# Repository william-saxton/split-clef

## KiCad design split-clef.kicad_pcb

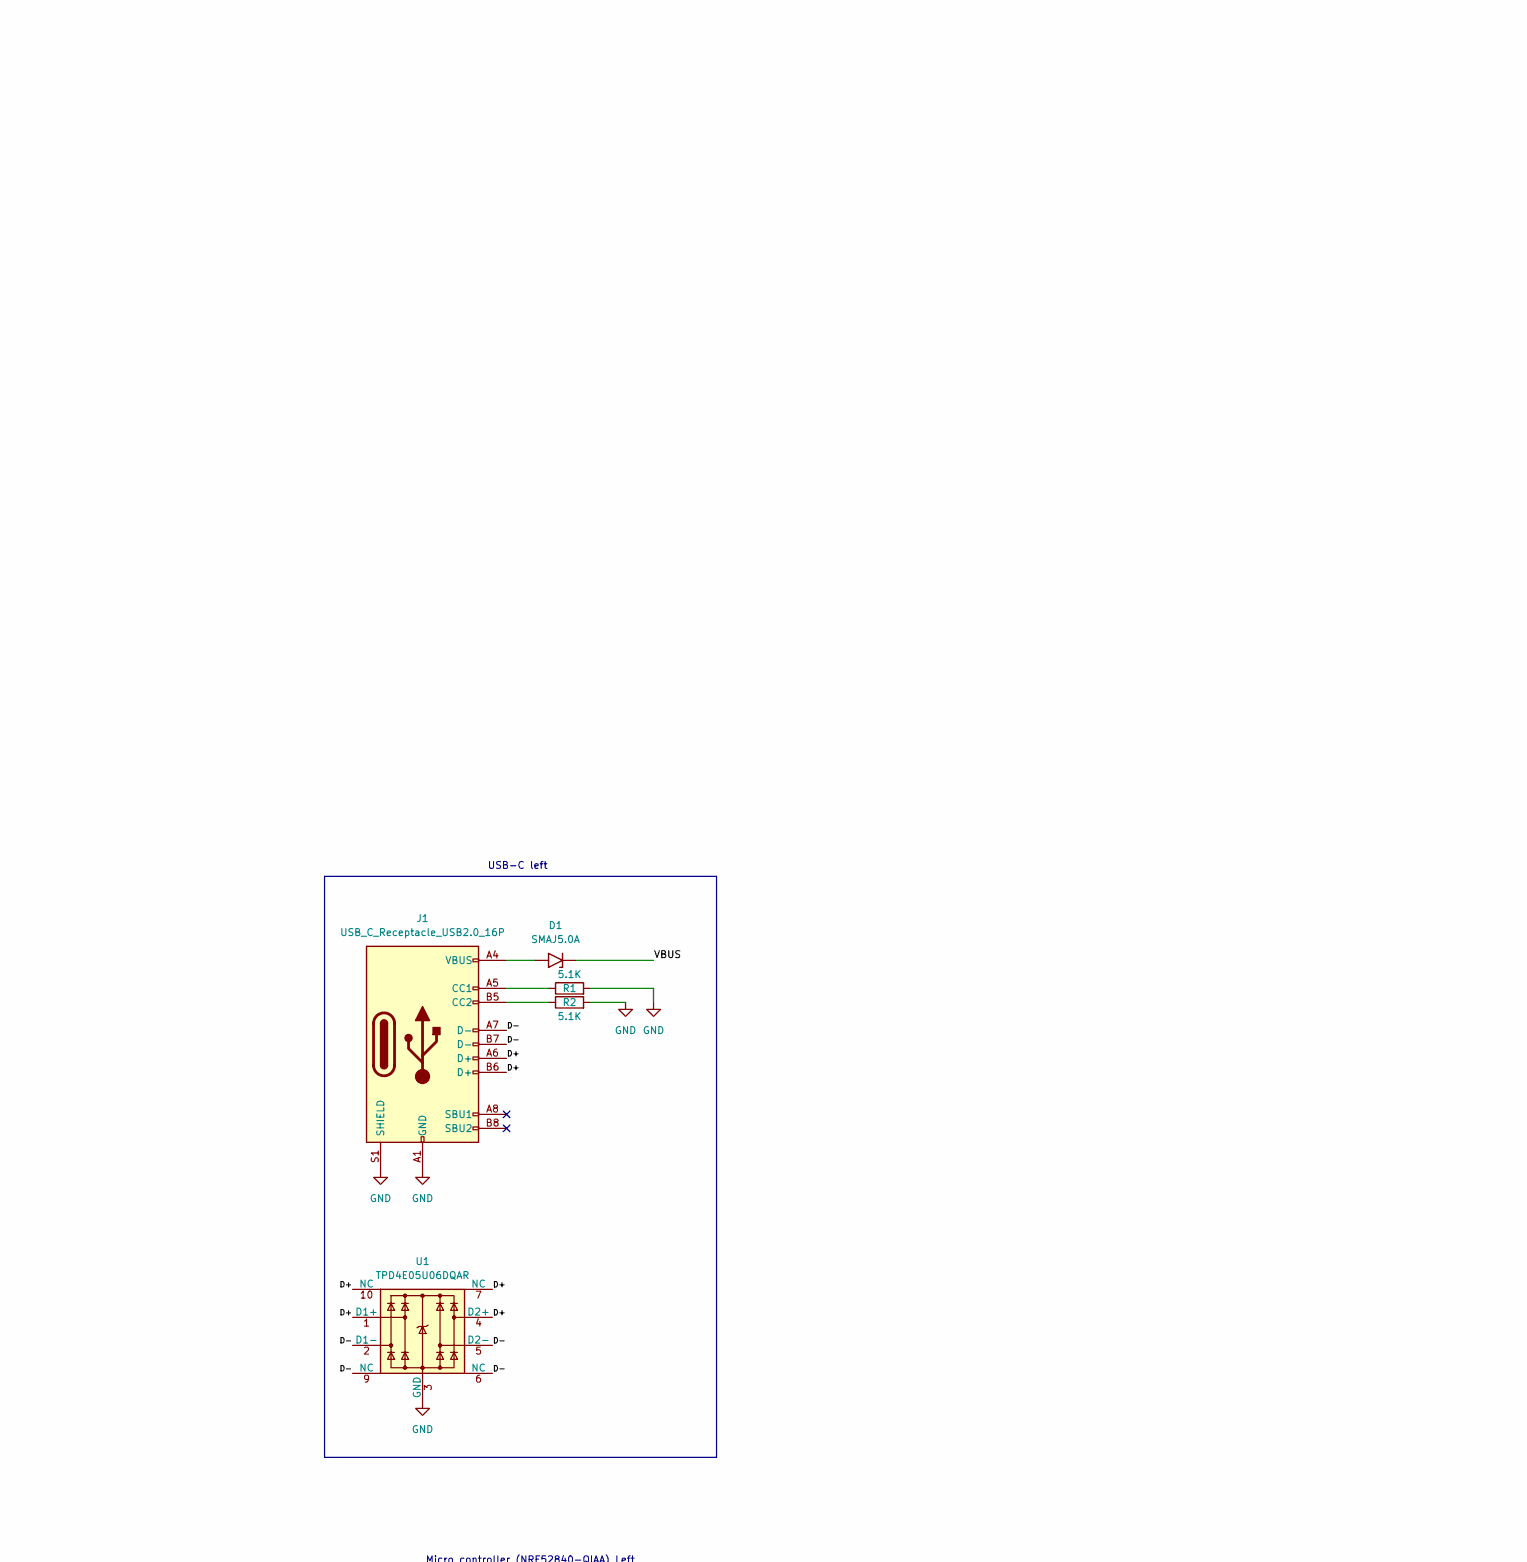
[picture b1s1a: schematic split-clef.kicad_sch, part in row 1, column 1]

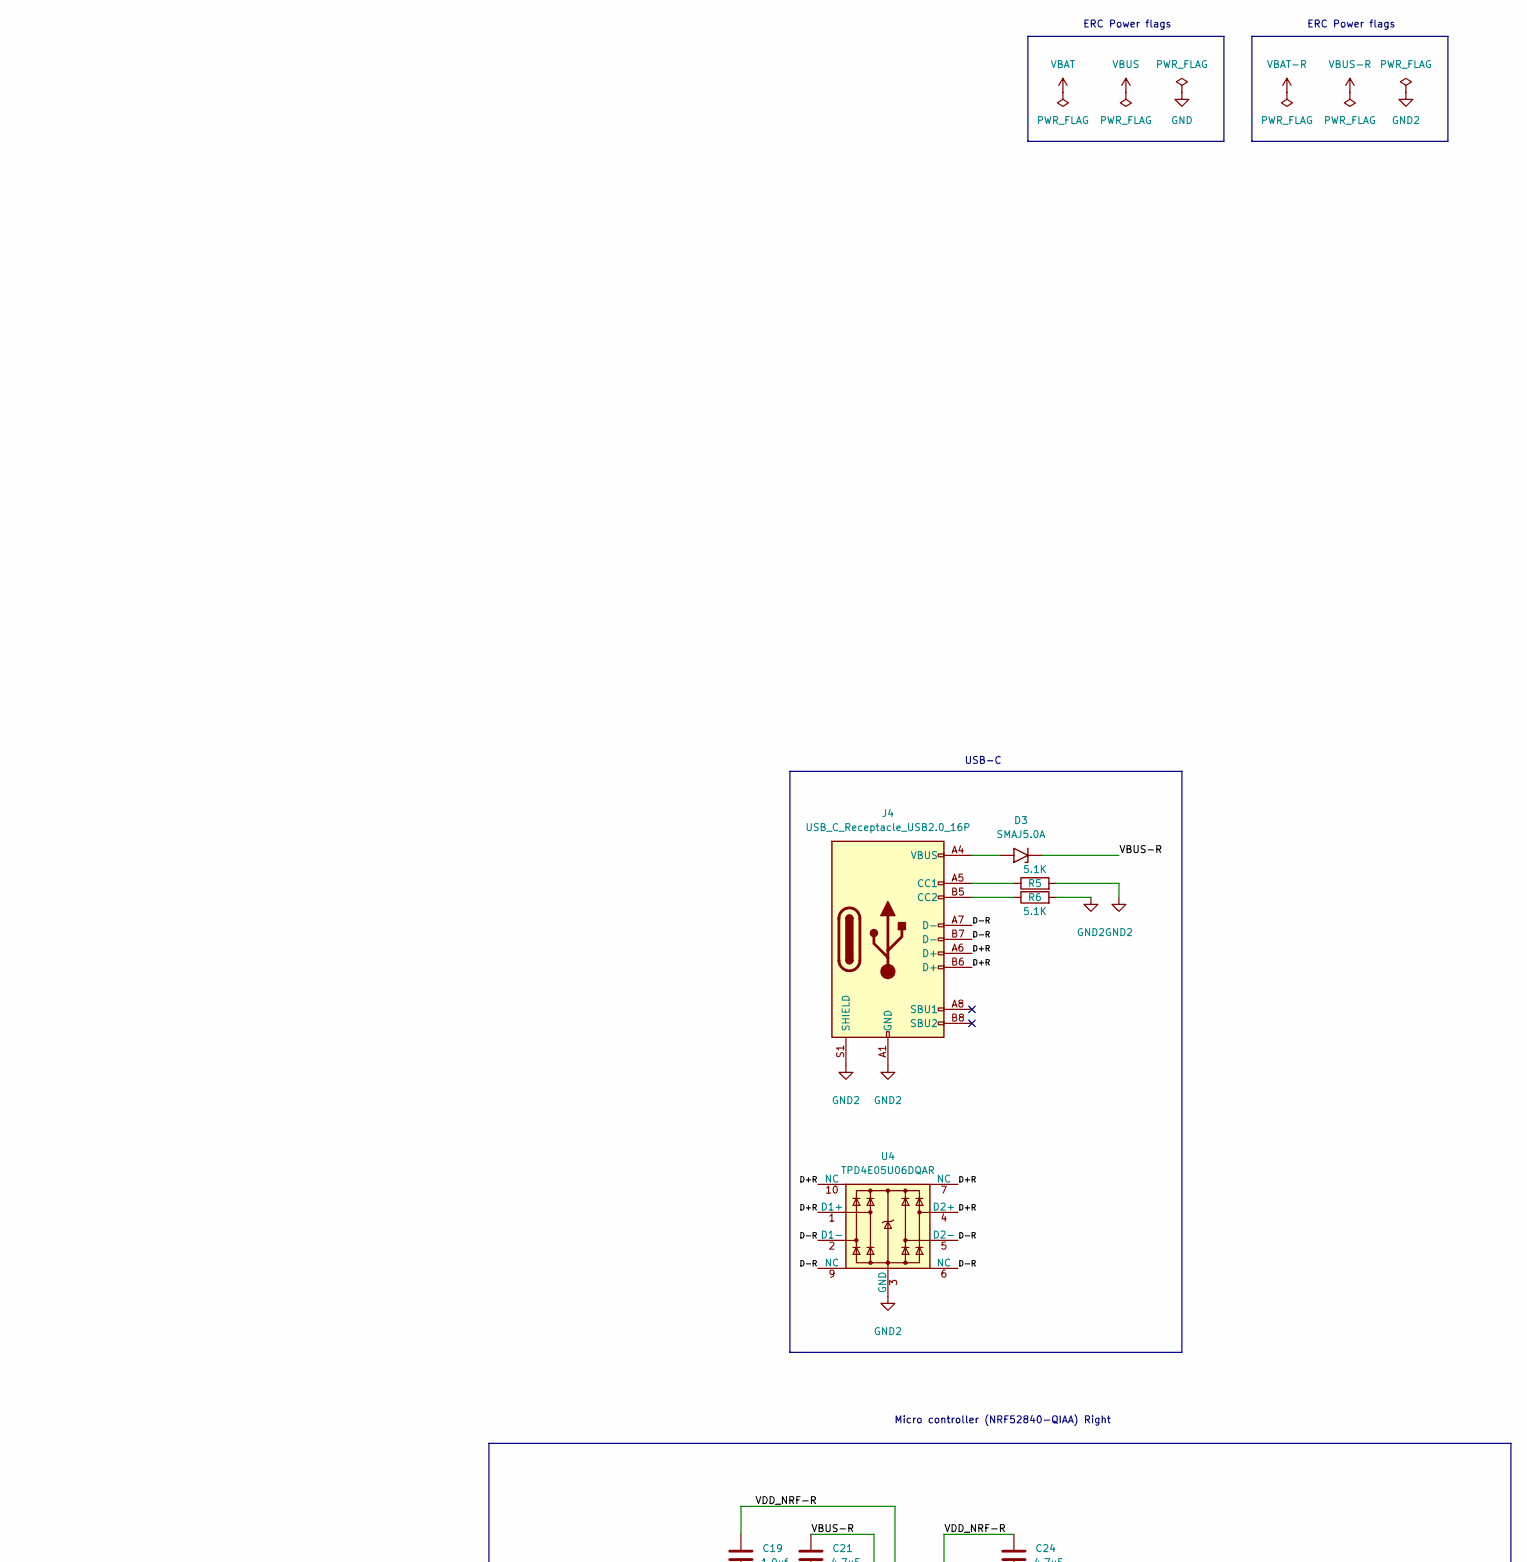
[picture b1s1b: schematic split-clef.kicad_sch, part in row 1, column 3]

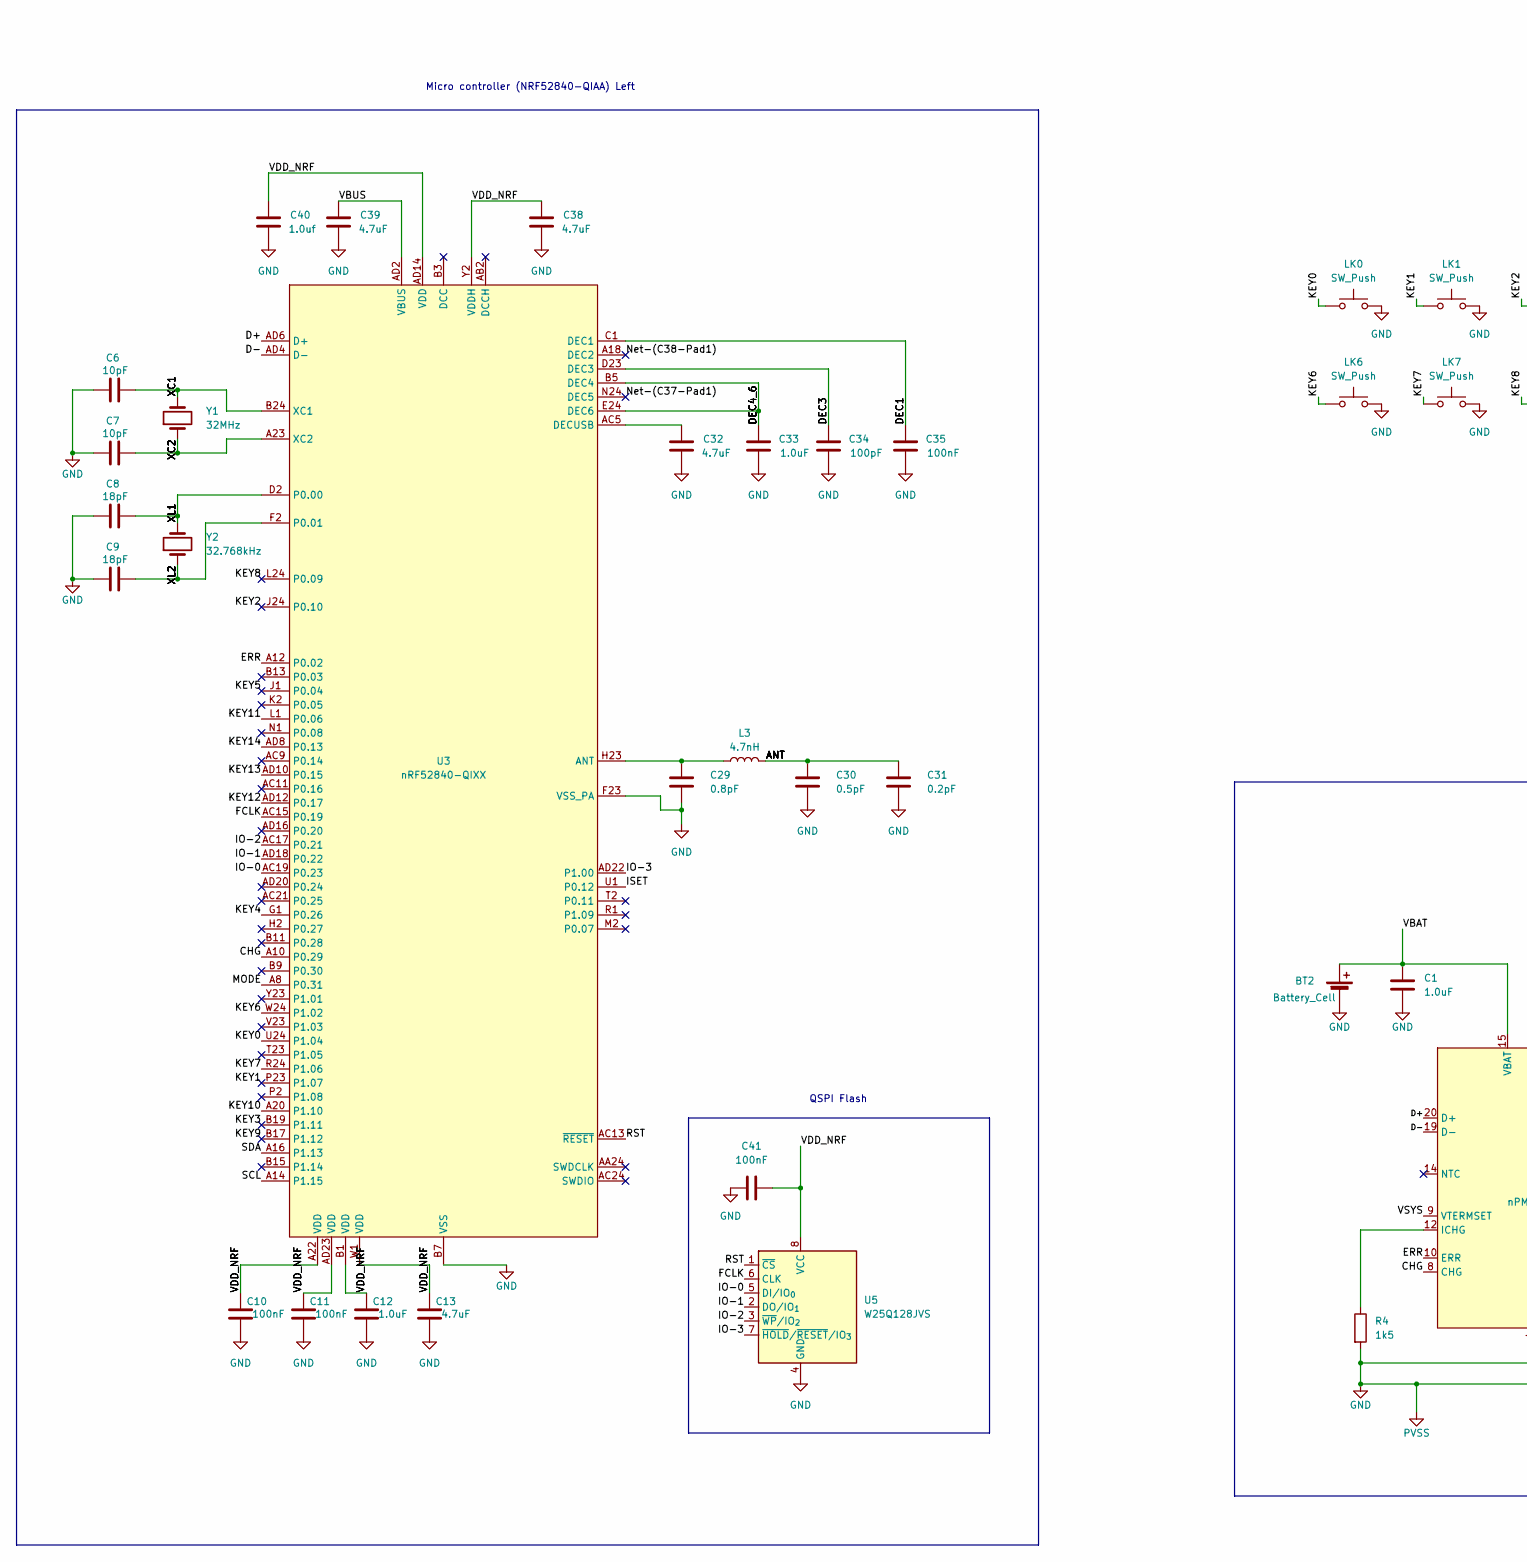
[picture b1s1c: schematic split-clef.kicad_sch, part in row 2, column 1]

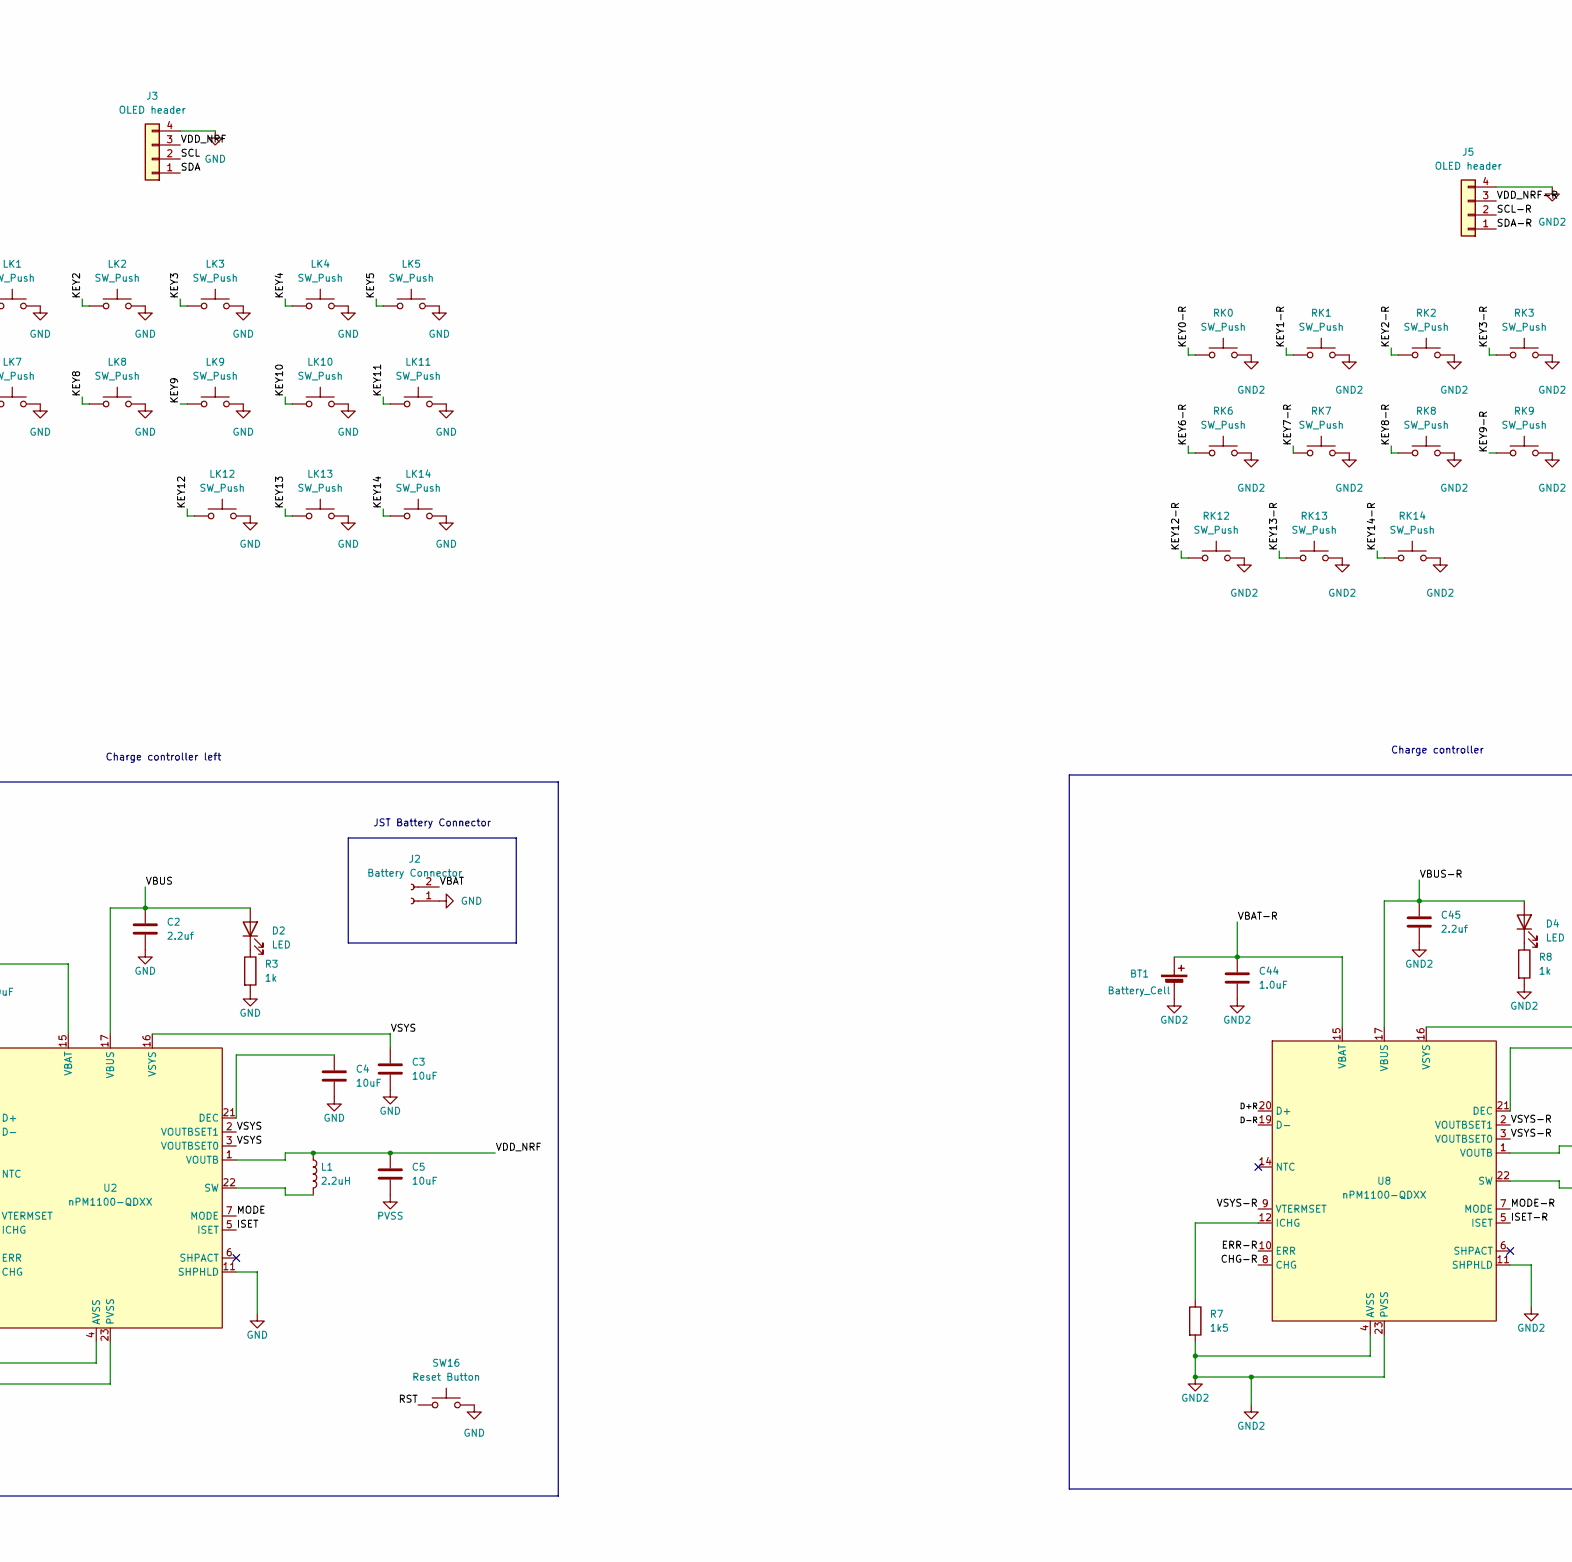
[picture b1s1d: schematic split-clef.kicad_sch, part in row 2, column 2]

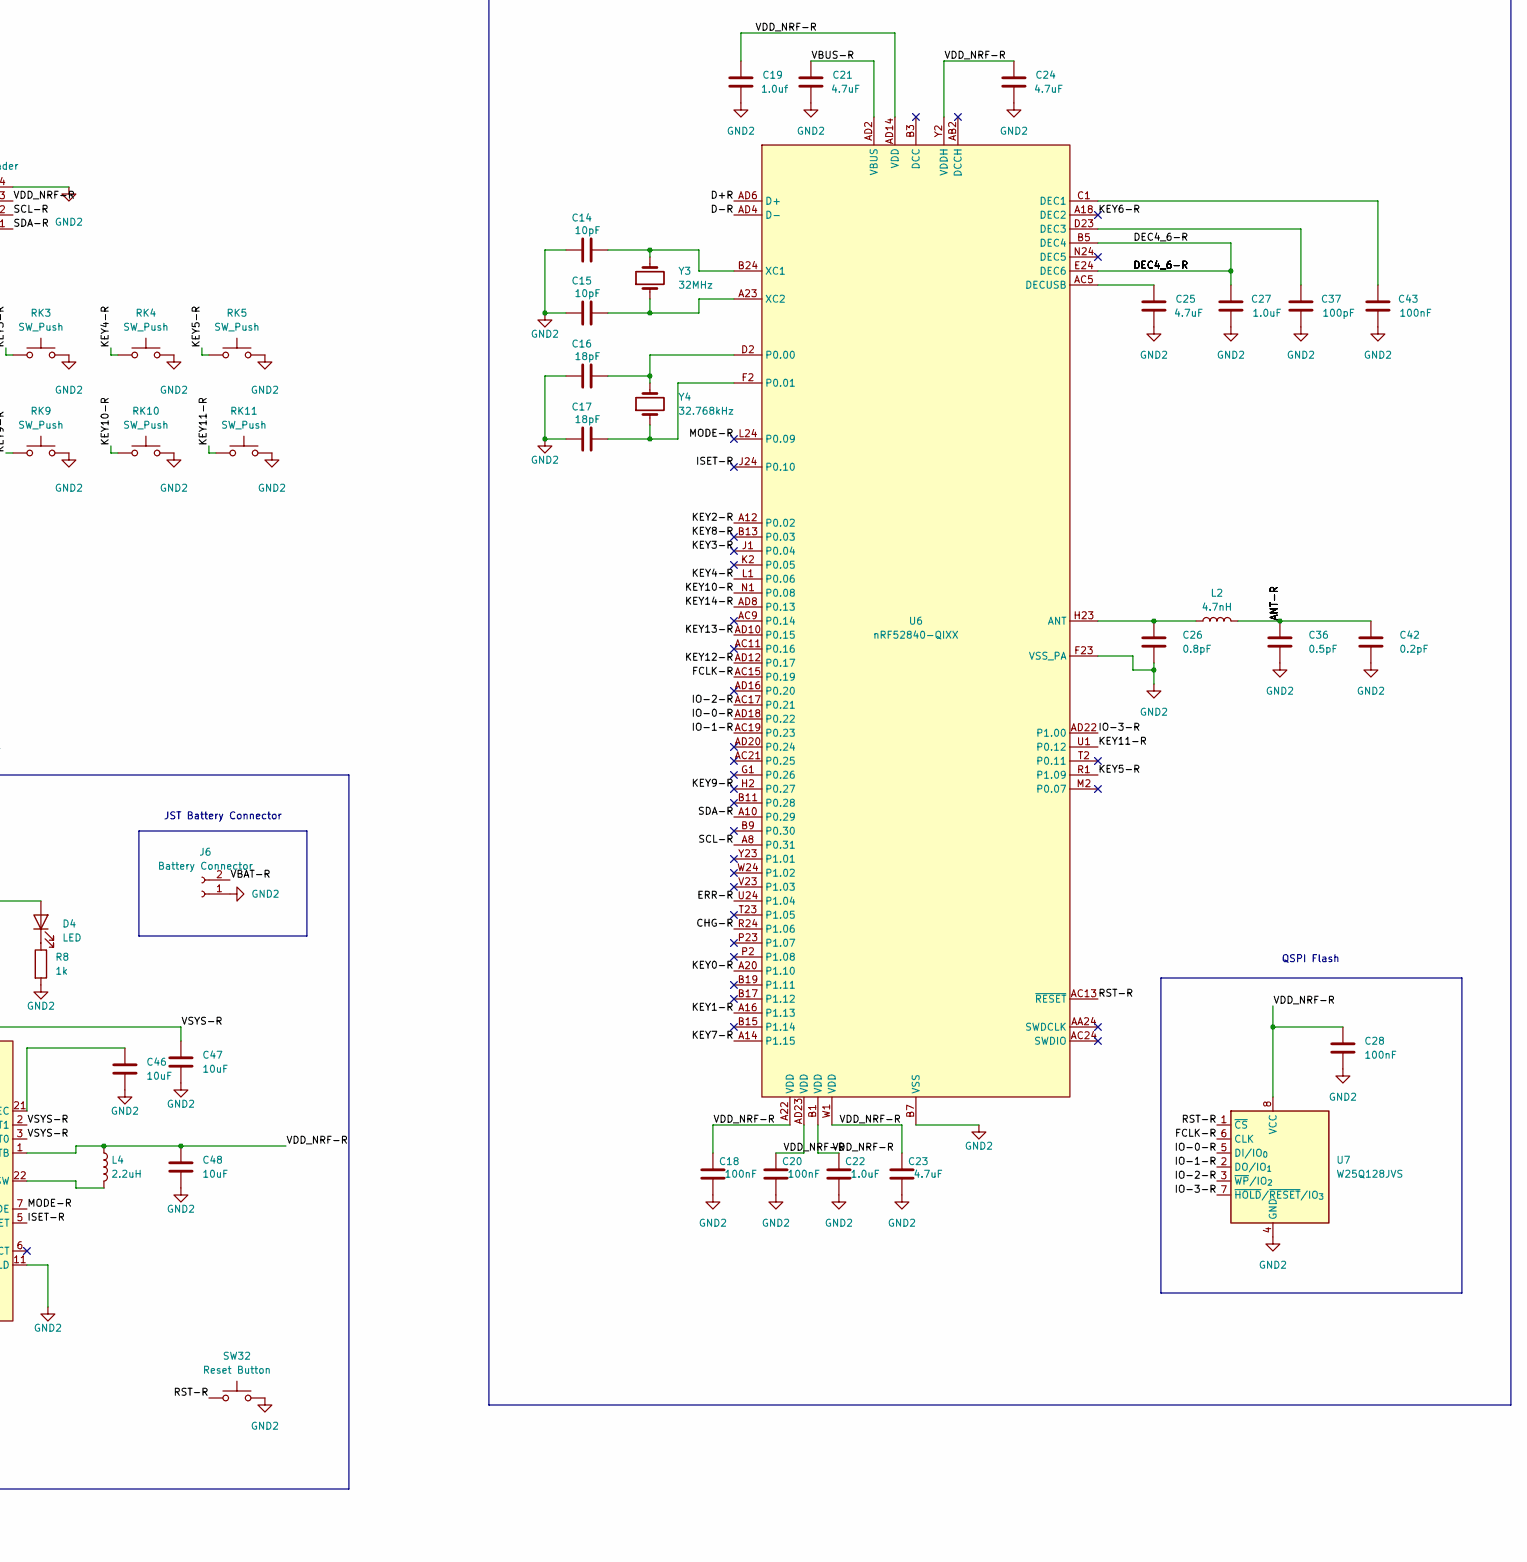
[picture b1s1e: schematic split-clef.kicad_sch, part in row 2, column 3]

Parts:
BT1, BT2: Battery_Cell
C1, C12, C22, C27, C33, C44: 1.0uF; C_0402_1005Metric
C2, C45: 2.2uf; C_0402_1005Metric
C3, C4, C5, C46, C47, C48: 10uF; C_0402_1005Metric
C6, C7, C14, C15: 10pF; C_0402_1005Metric
C8, C9, C16, C17: 18pF; C_0402_1005Metric
C10, C11, C18, C20, C28, C35, C41, C43: 100nF; C_0402_1005Metric
C13, C21, C23, C24, C25, C32, C38, C39: 4.7uF; C_0402_1005Metric
C19, C40: 1.0uf; C_0402_1005Metric
C26, C29: 0.8pF; C_0402_1005Metric
C30, C36: 0.5pF; C_0402_1005Metric
C31, C42: 0.2pF; C_0402_1005Metric
C34, C37: 100pF; C_0402_1005Metric
D1, D3: SMAJ5.0A; D_SMA
D2, D4: LED; LED_0402_1005Metric
J1, J4: USB_C_Receptacle_USB2.0_16P; USB_C_Receptacle_GCT_USB4105-xx-A_16P_TopMnt_Horizontal
J2, J6: Battery Connector; JST_PH_S2B-PH-K_1x02_P2.00mm_Horizontal
J3, J5: OLED header; OLED_v2
L1, L4: 2.2uH; L_0805_2012Metric
L2, L3: 4.7nH; L_0402_1005Metric
LK0, LK1, LK2, LK3, LK4, LK5, LK6, LK7, LK8, LK9, LK10, LK11, LK12, LK13, LK14: SW_Push; ChocV1_V2_Hotswap
R1, R2, R5, R6: 5.1K; R_0603_1608Metric
R3, R8: 1k; R_0402_1005Metric
R4, R7: 1k5; R_0402_1005Metric
RK0, RK1, RK2, RK3, RK4, RK5, RK6, RK7, RK8, RK9, RK10, RK11, RK12, RK13, RK14: SW_Push; ChocV1_V2_Hotswap
SW16, SW32: Reset Button; SW_TS-1088-AR02016
U1, U4: TPD4E05U06DQAR; USON-10_2.5x1.0mm_P0.5mm; JLCPCB Part # C138714
U2, U8: nPM1100-QDXX; QFN-24-1EP_4x4mm_P0.5mm_EP2.6x2.6mm_ThermalVias
U3, U6: nRF52840-QIXX; Nordic_AQFN-73-1EP_7x7mm_P0.5mm
U5, U7: W25Q128JVS; SOIC-8_5.3x5.3mm_P1.27mm
Y1, Y3: 32MHz; Crystal_SMD_2016-4Pin_2.0x1.6mm
Y2, Y4: 32.768kHz; Crystal_SMD_2012-2Pin_2.0x1.2mm

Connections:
/ANT: C30.1, C31.1, L3.2; also elsewhere on the board
/ANT-R: C36.1, C42.1, L2.2; also elsewhere on the board
/CHG: U2.8 (CHG), U3.A10 (P0.29)
/CHG-R: U6.R24 (P1.06), U8.8 (CHG)
/D+: J1.A6 (D+), J1.B6 (D+), U1.1 (D1+), U1.4 (D2+), U1.7 (NC), U1.10 (NC), U2.20 (D+), U3.AD6 (D+)
/D+R: J4.A6 (D+), J4.B6 (D+), U4.1 (D1+), U4.4 (D2+), U4.7 (NC), U4.10 (NC), U6.AD6 (D+), U8.20 (D+)
/D-: J1.A7 (D-), J1.B7 (D-), U1.2 (D1-), U1.5 (D2-), U1.6 (NC), U1.9 (NC), U2.19 (D-), U3.AD4 (D-)
/D-R: J4.A7 (D-), J4.B7 (D-), U4.2 (D1-), U4.5 (D2-), U4.6 (NC), U4.9 (NC), U6.AD4 (D-), U8.19 (D-)
/DEC1: C35.1, U3.C1 (DEC1)
/DEC3: C34.1, U3.D23 (DEC3)
/DEC4_6: C33.1, U3.B5 (DEC4), U3.E24 (DEC6)
/DEC4_6-R: C27.1, U6.B5 (DEC4), U6.E24 (DEC6); also elsewhere on the board
/ERR: U2.10 (ERR), U3.A12 (P0.02)
/ERR-R: U6.U24 (P1.04), U8.10 (ERR)
/FCLK: U3.AC15 (P0.19), U5.6 (CLK)
/FCLK-R: U6.AC15 (P0.19), U7.6 (CLK)
/IO-0: U3.AC19 (P0.23), U5.5 (DI/IO_{0})
/IO-0-R: U6.AD18 (P0.22), U7.5 (DI/IO_{0})
/IO-1: U3.AD18 (P0.22), U5.2 (DO/IO_{1})
/IO-1-R: U6.AC19 (P0.23), U7.2 (DO/IO_{1})
/IO-2: U3.AC17 (P0.21), U5.3 (~WP/IO_{2})
/IO-2-R: U6.AC17 (P0.21), U7.3 (~WP/IO_{2})
/IO-3: U3.AD22 (P1.00), U5.7 (~HOLD/~RESET/IO_{3})
/IO-3-R: U6.AD22 (P1.00), U7.7 (~HOLD/~RESET/IO_{3})
/ISET: U2.5 (ISET), U3.U1 (P0.12)
/ISET-R: U6.J24 (P0.10), U8.5 (ISET)
/KEY0: LK0.1, U3.U24 (P1.04)
/KEY0-R: RK0.1, U6.A20 (P1.10)
/KEY1: LK1.1, U3.P23 (P1.07)
/KEY1-R: RK1.1, U6.A16 (P1.13)
/KEY2: LK2.1, U3.J24 (P0.10)
/KEY2-R: RK2.1, U6.A12 (P0.02)
/KEY3: LK3.1, U3.B19 (P1.11)
/KEY3-R: RK3.1, U6.J1 (P0.04)
/KEY4: LK4.1, U3.G1 (P0.26)
/KEY4-R: RK4.1, U6.L1 (P0.06)
/KEY5: LK5.1, U3.J1 (P0.04)
/KEY5-R: RK5.1, U6.R1 (P1.09)
/KEY6: LK6.1, U3.W24 (P1.02)
/KEY6-R: RK6.1, U6.A18 (DEC2)
/KEY7: LK7.1, U3.R24 (P1.06)
/KEY7-R: RK7.1, U6.A14 (P1.15)
/KEY8: LK8.1, U3.L24 (P0.09)
/KEY8-R: RK8.1, U6.B13 (P0.03)
/KEY9: LK9.1, U3.B17 (P1.12)
/KEY9-R: RK9.1, U6.H2 (P0.27)
/KEY10: LK10.1, U3.A20 (P1.10)
/KEY10-R: RK10.1, U6.N1 (P0.08)
/KEY11: LK11.1, U3.L1 (P0.06)
/KEY11-R: RK11.1, U6.U1 (P0.12)
/KEY12: LK12.1, U3.AD12 (P0.17)
/KEY12-R: RK12.1, U6.AD12 (P0.17)
/KEY13: LK13.1, U3.AD10 (P0.15)
/KEY13-R: RK13.1, U6.AD10 (P0.15)
/KEY14: LK14.1, U3.AD8 (P0.13)
/KEY14-R: RK14.1, U6.AD8 (P0.13)
/MODE: U2.7 (MODE), U3.A8 (P0.31)
/MODE-R: U6.L24 (P0.09), U8.7 (MODE)
/Net-(C37-Pad1): U3.N24 (DEC5)
/Net-(C38-Pad1): U3.A18 (DEC2)
/RST: SW16.1, U3.AC13 (~RESET), U5.1 (~CS)
/RST-R: SW32.1, U6.AC13 (~RESET), U7.1 (~CS)
/SCL: J3.2, U3.A14 (P1.15)
/SCL-R: J5.2, U6.A8 (P0.31)
/SDA: J3.1, U3.A16 (P1.13)
/SDA-R: J5.1, U6.A10 (P0.29)
/VDD_NRF: C5.1, C10.1, C11.1, C12.1, C13.1, C38.1, C40.1, C41.2, J3.3, L1.1, U2.1 (VOUTB), U3.A22 (VDD), U3.AD14 (VDD), U3.AD23 (VDD), U3.B1 (VDD), U3.W1 (VDD), U3.Y2 (VDDH), U5.8 (VCC)
/VDD_NRF-R: C18.1, C19.1, C20.1, C22.1, C23.1, C24.1, C28.1, C48.1, J5.3, L4.1, U6.A22 (VDD), U6.AD14 (VDD), U6.AD23 (VDD), U6.B1 (VDD), U6.W1 (VDD), U6.Y2 (VDDH), U7.8 (VCC), U8.1 (VOUTB)
/VSYS: C3.1, U2.2 (VOUTBSET1), U2.3 (VOUTBSET0), U2.9 (VTERMSET), U2.16 (VSYS)
/VSYS-R: C47.1, U8.2 (VOUTBSET1), U8.3 (VOUTBSET0), U8.9 (VTERMSET), U8.16 (VSYS)
/XC1: C6.2, U3.B24 (XC1), Y1.2
/XC2: C7.2, U3.A23 (XC2), Y1.1
/XL1: C8.2, U3.D2 (P0.00), Y2.2
/XL2: C9.2, U3.F2 (P0.01), Y2.1
GND: BT2.2 (-), C1.2, C2.2, C3.2, C4.2, C5.2, C6.1, C7.1, C8.1, C9.1, C10.2, C11.2, C12.2, C13.2, C29.2, C30.2, C31.2, C32.2, C33.2, C34.2, C35.2, C38.2, C39.2, C40.2, C41.1, J1.A1 (GND), J1.A12 (GND), J1.B1 (GND), J1.B12 (GND), J1.S1 (SHIELD), J2.1, J3.4, LK0.2, LK1.2, LK2.2, LK3.2, LK4.2, LK5.2, LK6.2, LK7.2, LK8.2, LK9.2, LK10.2, LK11.2, LK12.2, LK13.2, LK14.2, R1.2, R2.2, R3.2, R4.2, SW16.2, U1.3 (GND), U1.8 (GND), U2.4 (AVSS), U2.11 (SHPHLD), U2.23 (PVSS), U2.25 (AVSS), U3.B7 (VSS), U3.EP (VSS), U3.F23 (VSS_PA), U5.4 (GND)
GND2: BT1.2 (-), C14.1, C15.1, C16.1, C17.1, C18.2, C19.2, C20.2, C21.2, C22.2, C23.2, C24.2, C25.2, C26.2, C27.2, C28.2, C36.2, C37.2, C42.2, C43.2, C44.2, C45.2, C46.2, C47.2, C48.2, J4.A1 (GND), J4.A12 (GND), J4.B1 (GND), J4.B12 (GND), J4.S1 (SHIELD), J5.4, J6.1, R5.2, R6.2, R7.2, R8.2, RK0.2, RK1.2, RK2.2, RK3.2, RK4.2, RK5.2, RK6.2, RK7.2, RK8.2, RK9.2, RK10.2, RK11.2, RK12.2, RK13.2, RK14.2, SW32.2, U4.3 (GND), U4.8 (GND), U6.B7 (VSS), U6.EP (VSS), U6.F23 (VSS_PA), U7.4 (GND), U8.4 (AVSS), U8.11 (SHPHLD), U8.23 (PVSS), U8.25 (AVSS); also elsewhere on the board
unnamed: D1.2 (A2), J1.A4 (VBUS), J1.A9 (VBUS), J1.B4 (VBUS), J1.B9 (VBUS)
unnamed: D2.1 (K), R3.1
unnamed: D3.2 (A2), J4.A4 (VBUS), J4.A9 (VBUS), J4.B4 (VBUS), J4.B9 (VBUS)
unnamed: D4.1 (K), R8.1
unnamed: J1.A5 (CC1), R1.1
unnamed: J1.B5 (CC2), R2.1
unnamed: J4.A5 (CC1), R5.1
unnamed: J4.B5 (CC2), R6.1
unnamed: C4.1, U2.21 (DEC)
unnamed: R4.1, U2.12 (ICHG)
unnamed: L1.2, U2.22 (SW)
unnamed: C29.1, L3.1, U3.H23 (ANT)
unnamed: C32.1, U3.AC5 (DECUSB)
unnamed: C26.1, L2.1, U6.H23 (ANT)
unnamed: C43.1, U6.C1 (DEC1)
unnamed: C37.1, U6.D23 (DEC3)
unnamed: C25.1, U6.AC5 (DECUSB)
unnamed: C16.2, U6.D2 (P0.00), Y4.2
unnamed: C17.2, U6.F2 (P0.01), Y4.1
unnamed: C14.2, U6.B24 (XC1), Y3.2
unnamed: C15.2, U6.A23 (XC2), Y3.1
unnamed: C46.1, U8.21 (DEC)
unnamed: R7.1, U8.12 (ICHG)
unnamed: L4.2, U8.22 (SW)
VBAT: BT2.1 (+), C1.1, J2.2, U2.15 (VBAT)
VBAT-R: BT1.1 (+), C44.1, J6.2, U8.15 (VBAT)
VBUS: C2.1, C39.1, D1.1 (A1), D2.2 (A), U2.17 (VBUS), U3.AD2 (VBUS)
VBUS-R: C21.1, C45.1, D3.1 (A1), D4.2 (A), U6.AD2 (VBUS), U8.17 (VBUS)

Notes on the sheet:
ERC Power flags
JST Battery Connector
Charge controller
USB-C
Micro controller (NRF52840-QIAA) Right
QSPI Flash
Charge controller left
Micro controller (NRF52840-QIAA) Left
USB-C left

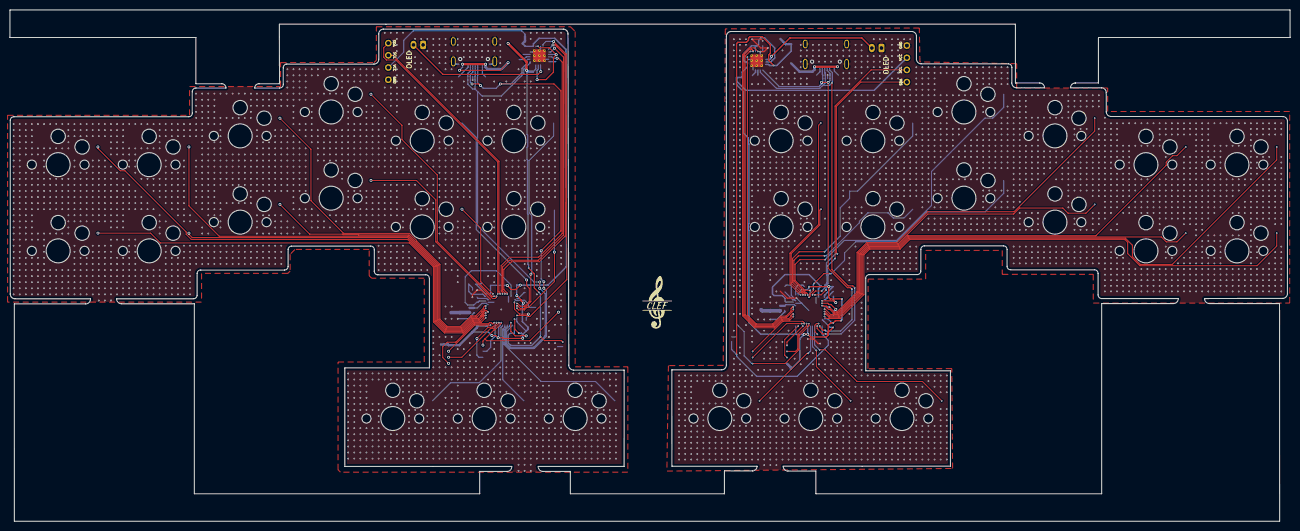
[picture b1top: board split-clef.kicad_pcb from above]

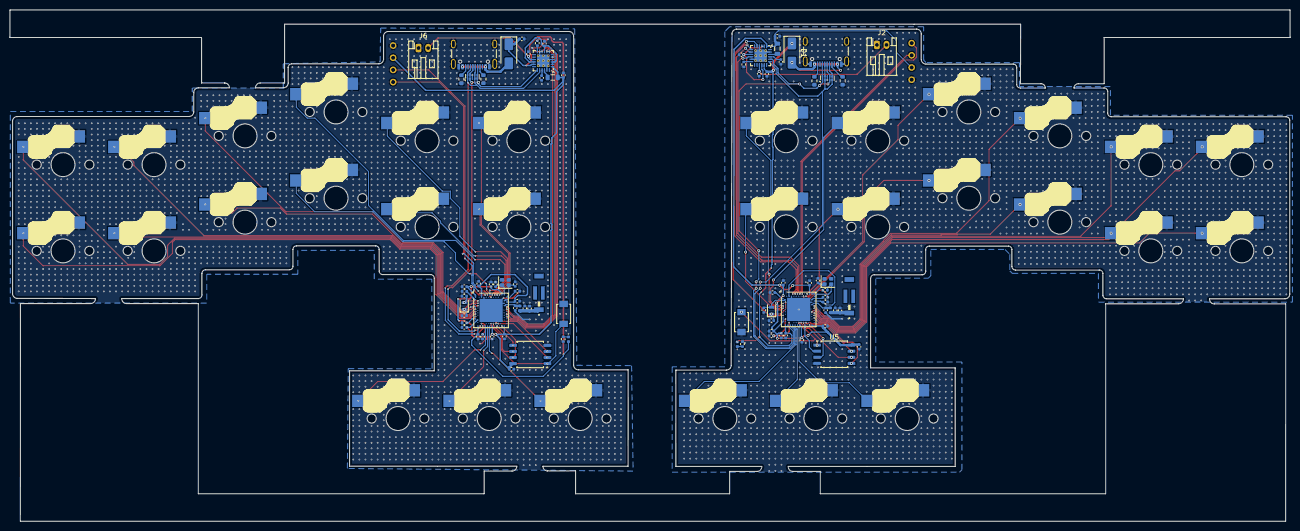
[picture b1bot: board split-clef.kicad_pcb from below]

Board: 2 copper layers, 267.2 x 106.8 mm, 119 parts (85 on the bottom side), 102 nets.

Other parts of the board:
ANT: ANTENNA_2450AT43B100E
ANT#2: ANTENNA_2450AT43B100E
C37#2: 100pF; C_0402_1005Metric
LOGO: LOGO; logo
LOGO#2: LOGO; logo

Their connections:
/ANT: ANT.1; also elsewhere on the board
/ANT-R: ANT#2.1; also elsewhere on the board
/DEC4_6-R: C37#2.2; also elsewhere on the board
GND2: C37#2.1; also elsewhere on the board

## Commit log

2025-05-03 init
2025-05-04 updated to diodeless design and added logo.
2025-05-04 added GND zones
2025-05-04 fixing fill zones
2025-05-06 first iteration done
2025-05-07 jlcpcb
2025-05-23 v1.0
2025-05-31 v2 finished, need to generate prods files
